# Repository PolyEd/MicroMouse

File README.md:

Hello! This is the central readme for the PolyEd MicroMouse Project. \
This file is a compilation of general (non-code specific) information relating to the project.

Our inspiration: \
[The Fastest Maze-Solving Competition On Earth](https://www.youtube.com/watch?v=ZMQbHMgK2rw)

The conference we will attend: \
[APEC](https://apec-conf.org/)

Rules:
- [The conference rules](https://s3.us-east-1.amazonaws.com/apec-conf-images/APEC_Policies_And_Procedures_Rev_7-3_2022-09-02.pdf) —\
  See page 15 "Minimum Age Policy" which implies there is no minimum age for the MicroMouse contest.
- [An old set of MicroMouse rules (revision 2009)](http://micromouseusa.com/wp-content/uploads/2013/10/APEC-Rules.pdf)

**Important** files to read before working with the Arduino code or using it:
- [I2C README](I2C-README.md)
- [Info about the plotting library used in this project](PLOTTER-README.md)

<!--
---
Also [Nim](https://nim-lang.org/) 😃
--><!--I (Joshua) commented this out to not be beligerent, please leave it in here in this form though, just for fun-->

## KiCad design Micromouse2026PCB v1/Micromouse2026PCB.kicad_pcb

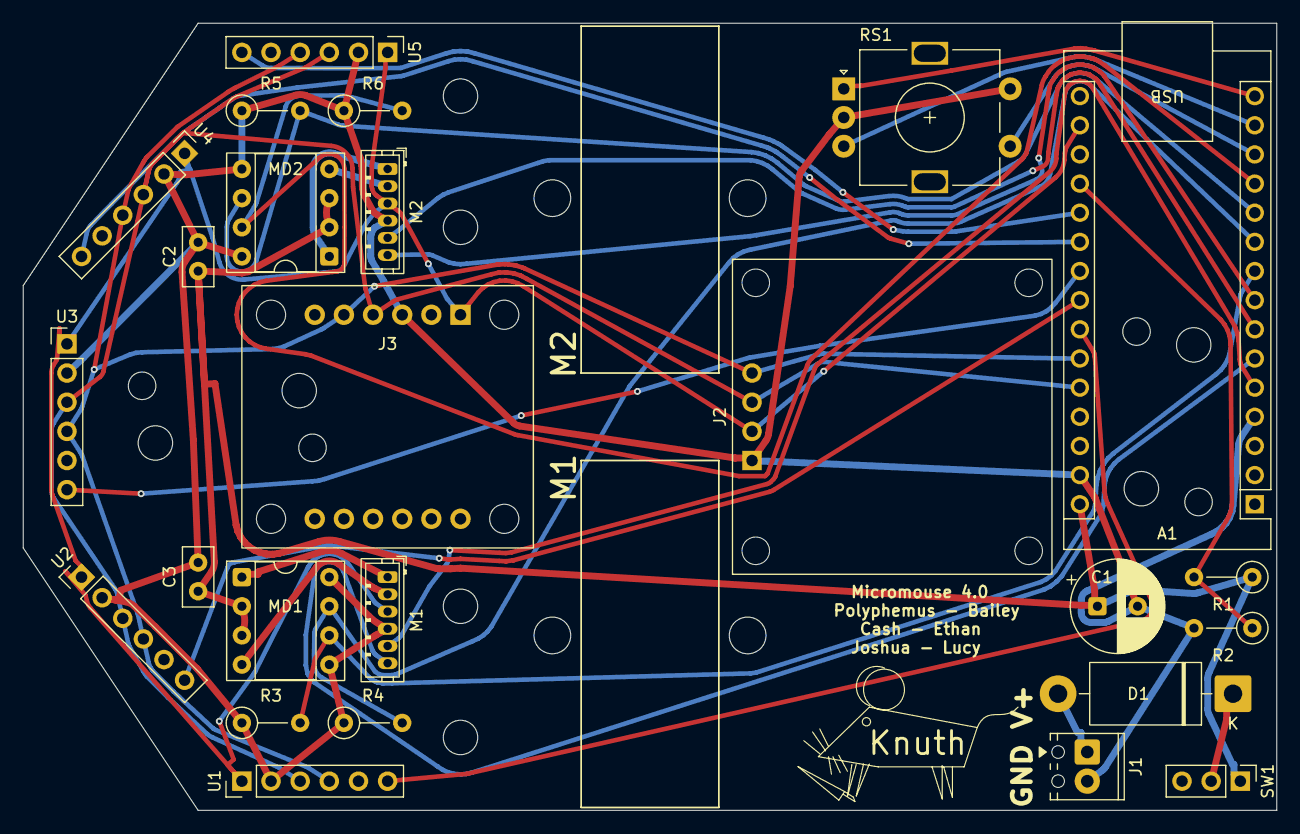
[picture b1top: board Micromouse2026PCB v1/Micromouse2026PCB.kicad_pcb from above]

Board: 2 copper layers, 109.2 x 68.6 mm, 25 parts (0 on the bottom side), 28 nets.

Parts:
A1: Arduino_Nano_ESP32; Arduino_Nano
C1: 470 µF (16v); CP_Radial_D8.0mm_P3.50mm
C2, C3: 100 nF; C_Disc_D5.0mm_W2.5mm_P2.50mm
D1: 1N5822; D_DO-201AD_P15.24mm_Horizontal
J1: Power Terminal; TerminalBlock_Phoenix_MPT-0,5-2-2.54_1x02_P2.54mm_Horizontal
J2: i2c OLED; OLED_0.96_SSD1306_I2C
J3: BNO085; Adafruit_BNO085
M1, M2: JST_ZH_B6B-ZR_1x06_P1.50mm_Vertical
MD1, MD2: DIP-8_W7.62mm_Socket
R1: 20k; R_Axial_DIN0207_L6.3mm_D2.5mm_P5.08mm_Vertical
R2, R3, R4, R5, R6: 10k; R_Axial_DIN0207_L6.3mm_D2.5mm_P5.08mm_Vertical
RS1: RotaryEncoder_Switch; RotaryEncoder_Alps_EC11E-Switch_Vertical_H20mm
SW1: PowerSW; PinHeader_1x03_P2.54mm_Vertical
U1, U2, U3, U4, U5: PinHeader_1x06_P2.54mm_Vertical

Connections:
+3.3V: A1.17 (3V3), J2.2, J3.1, M1.3 (VCC), M2.3 (VCC), U1.1 (VIN), U2.1 (VIN), U3.1 (VIN), U4.1 (VIN), U5.1 (VIN)
/SCL: A1.26 (A7), J2.3, J3.4, U1.3 (SCL), U2.3 (SCL), U3.3 (SCL), U4.3 (SCL), U5.3 (SCL)
/SDA: A1.25 (A6), J2.4, J3.5, U1.4 (SDA), U2.4 (SDA), U3.4 (SDA), U4.4 (SDA), U5.4 (SDA)
GND: A1.4 (GND), A1.29 (GND), C1.2, C2.2, C3.2, J1.2, J2.1, J3.3, M1.4 (GND), M2.4 (GND), MD1.5 (GND), MD1.8 (GND), MD2.5 (GND), MD2.8 (GND), R2.2, R3.1, R4.1, R5.1, R6.1, RS1.C, RS1.S2, U1.2 (GND), U2.2 (GND), U3.2 (GND), U4.2 (GND), U5.2 (GND)
unnamed: A1.19 (A0), R1.2, R2.1
unnamed: A1.20 (A1), U5.6 (XSHUT)
unnamed: A1.21 (A2), U4.6 (XSHUT)
unnamed: A1.22 (A3), U3.6 (XSHUT)
unnamed: A1.5 (D2), M1.5 (OA)
unnamed: A1.6 (D3), M1.6 (OB)
unnamed: A1.7 (D4), M2.5 (OA)
unnamed: A1.8 (D5), M2.6 (OB)
unnamed: A1.9 (D6), MD1.6 (IA), R3.2
unnamed: A1.10 (D7), MD1.7 (IB), R4.2
unnamed: A1.11 (D8), MD2.6 (IA), R5.2
unnamed: A1.12 (D9), MD2.7 (IB), R6.2
unnamed: A1.13 (D10/CS), RS1.S1
unnamed: A1.14 (D11/COPI), RS1.B
unnamed: A1.15 (D12/CIPO), RS1.A
unnamed: A1.24 (SCL/A5), U1.6 (XSHUT)
unnamed: A1.23 (SDA/A4), U2.6 (XSHUT)
unnamed: A1.30 (VIN), C1.1, C2.1, C3.1, MD1.2 (VCC), MD1.3 (VCC), MD2.2 (VCC), MD2.3 (VCC), R1.1, SW1.1
unnamed: D1.2 (A), J1.1
unnamed: D1.1 (K), SW1.2
unnamed: M1.1 (MA), MD1.1 (OA)
unnamed: M1.2 (MB), MD1.4 (OB)
unnamed: M2.1 (MA), MD2.1 (OA)
unnamed: M2.2 (MB), MD2.4 (OB)

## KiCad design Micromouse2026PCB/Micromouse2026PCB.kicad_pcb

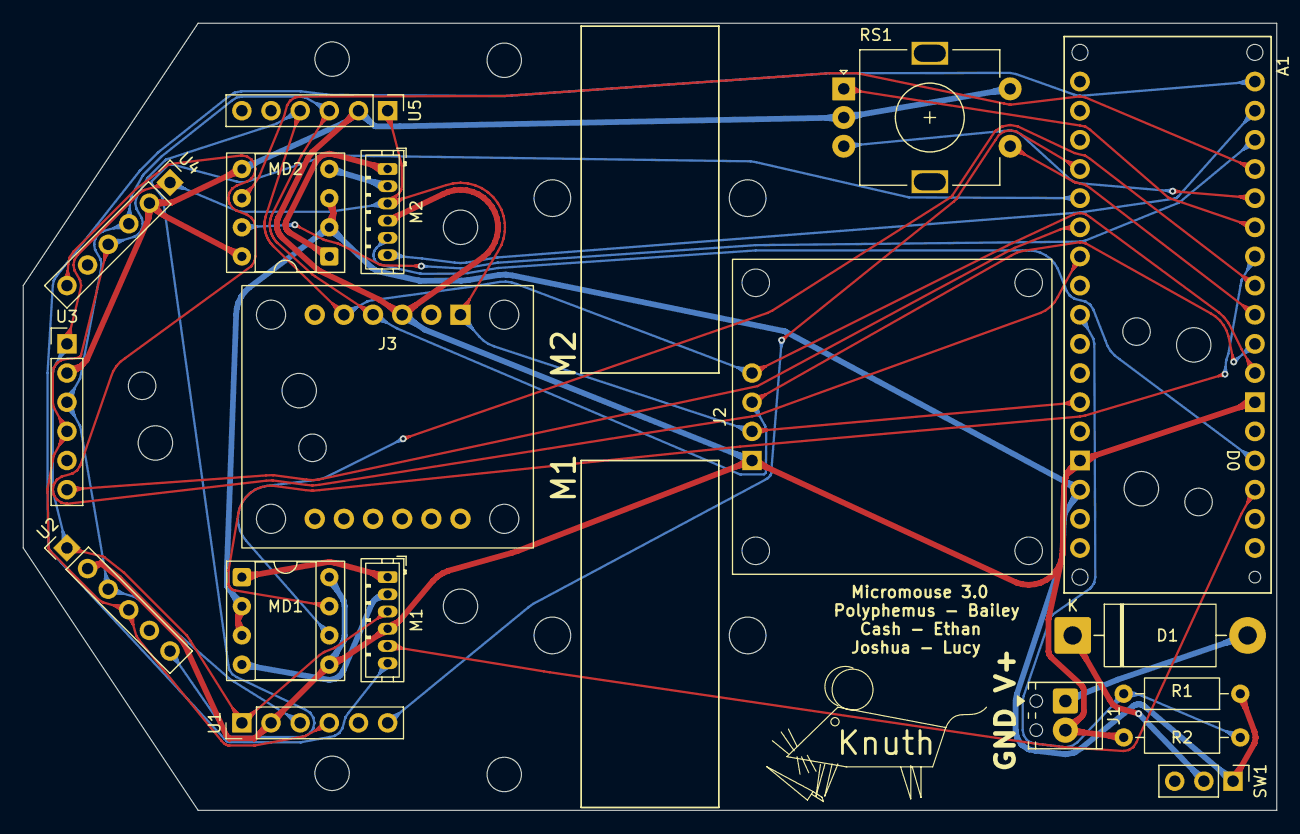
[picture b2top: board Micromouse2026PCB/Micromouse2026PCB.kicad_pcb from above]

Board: 2 copper layers, 109.2 x 68.6 mm, 18 parts (0 on the bottom side), 27 nets.

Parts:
A1: Arduino_Micro_Socket
D1: 1N5822; D_DO-201AD_P15.24mm_Horizontal
J1: Power Terminal; TerminalBlock_Phoenix_MPT-0,5-2-2.54_1x02_P2.54mm_Horizontal
J2: i2c OLED; OLED_0.96_SSD1306_I2C
J3: BNO085; Adafruit_BNO085
M1, M2: JST_ZH_B6B-ZR_1x06_P1.50mm_Vertical
MD1, MD2: DIP-8_W7.62mm_Socket
R1, R2: 10k; R_Axial_DIN0207_L6.3mm_D2.5mm_P10.16mm_Horizontal
RS1: RotaryEncoder_Switch; RotaryEncoder_Alps_EC11E-Switch_Vertical_H20mm
SW1: PowerSW; PinHeader_1x03_P2.54mm_Vertical
U1, U2, U3, U4, U5: PinHeader_1x06_P2.54mm_Vertical

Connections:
+5V: A1.5V, J2.2, J3.1, M1.3 (VCC), M2.3 (VCC), U1.1 (VIN), U2.1 (VIN), U3.1 (VIN), U4.1 (VIN), U5.1 (VIN)
/SCL: A1.D3 (D3/SCL), J2.3, J3.4, U1.3 (SCL), U2.3 (SCL), U3.3 (SCL), U4.3 (SCL), U5.3 (SCL)
/SDA: A1.D2 (D2/SDA), J2.4, J3.5, U1.4 (SDA), U2.4 (SDA), U3.4 (SDA), U4.4 (SDA), U5.4 (SDA)
GND: A1.GND1 (GND), A1.GND2 (GND), J1.2, J2.1, J3.3, M1.4 (GND), M2.4 (GND), MD1.5 (GND), MD1.8 (GND), MD2.5 (GND), MD2.8 (GND), R2.2, RS1.C, RS1.S2, U1.2 (GND), U2.2 (GND), U3.2 (GND), U4.2 (GND), U5.2 (GND)
unnamed: A1.D0 (D0/RX), M2.5 (OA)
unnamed: A1.D1 (D1/TX), M1.5 (OA)
unnamed: A1.D7 (D7_INT4), RS1.A
unnamed: A1.A5, R1.2, R2.1
unnamed: A1.D4, RS1.S1
unnamed: A1.D8, RS1.B
unnamed: D1.2 (A), J1.1
unnamed: D1.1 (K), SW1.2
unnamed: M1.1 (MA), MD1.1 (OA)
unnamed: M1.2 (MB), MD1.4 (OB)
unnamed: A1.D12, M1.6 (OB)
unnamed: M2.1 (MA), MD2.1 (OA)
unnamed: M2.2 (MB), MD2.4 (OB)
unnamed: A1.D11, M2.6 (OB)
unnamed: A1.D5, MD1.6 (IA)
unnamed: A1.D6, MD1.7 (IB)
unnamed: A1.D9, MD2.6 (IA)
unnamed: A1.D10, MD2.7 (IB)
unnamed: A1.VIN, MD1.2 (VCC), MD1.3 (VCC), MD2.2 (VCC), MD2.3 (VCC), R1.1, SW1.1
unnamed: A1.A0, U1.6 (XSHUT)
unnamed: A1.A1, U2.6 (XSHUT)
unnamed: A1.A2, U3.6 (XSHUT)
unnamed: A1.A3, U4.6 (XSHUT)

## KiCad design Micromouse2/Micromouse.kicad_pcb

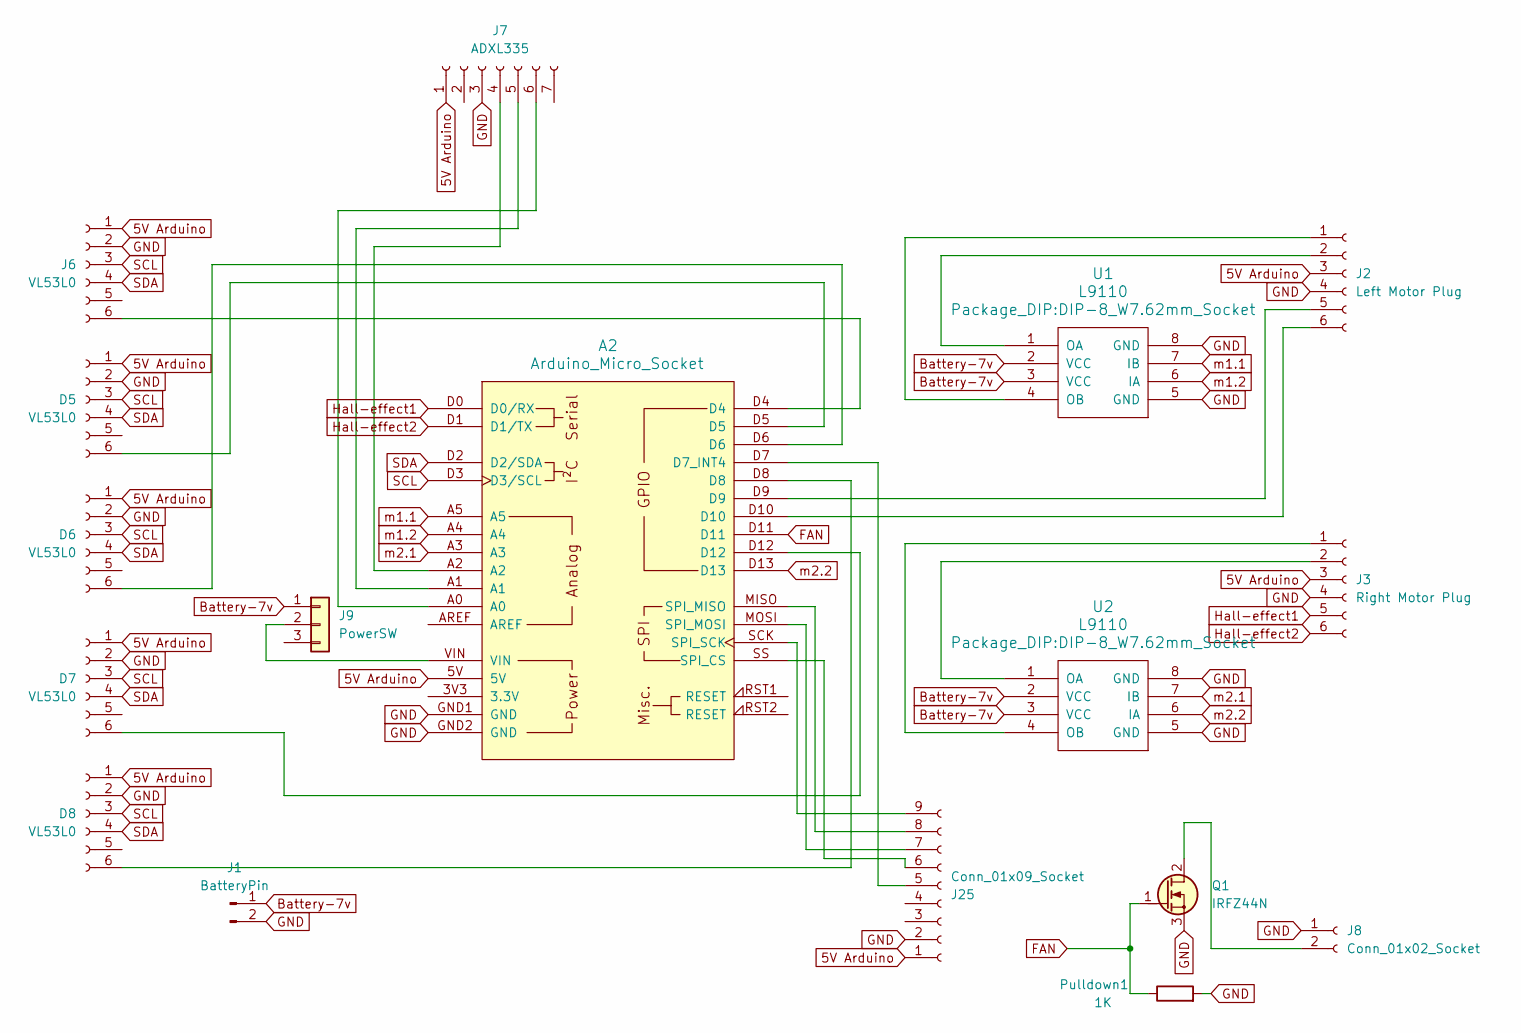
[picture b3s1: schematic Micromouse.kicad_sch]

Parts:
A2: Arduino_Micro_Socket
D5, D6, D7, D8: VL53L0; PinSocket_1x06_P2.54mm_Vertical
J1: BatteryPin; PinSocket_1x02_P2.54mm_Vertical
J2: Left Motor Plug; Wuerth_WR-WTB_64800611622_1x06_P1.50mm_Vertical
J3: Right Motor Plug; Wuerth_WR-WTB_64800611622_1x06_P1.50mm_Vertical
J6: VL53L0; PinSocket_1x06_P2.54mm_Vertical
J7: ADXL335; PinSocket_1x07_P2.54mm_Vertical
J8: Conn_01x02_Socket; JST_PH_B2B-PH-K_1x02_P2.00mm_Vertical
J9: PowerSW; PinHeader_1x03_P2.54mm_Vertical
J25: Conn_01x09_Socket; PinHeader_1x09_P2.54mm_Horizontal
Pulldown1: 1K; R_Axial_DIN0207_L6.3mm_D2.5mm_P7.62mm_Horizontal
Q1: IRFZ44N; TO-220-3_Horizontal_TabDown
U1, U2: L9110; DIP-8_W7.62mm_Socket

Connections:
5V Arduino: A2.5V, D5.1 (Vin), D6.1 (Vin), D7.1 (Vin), D8.1 (Vin), J2.3, J3.3, J6.1 (Vin), J7.1, J25.1
Battery-7v: J1.1, J9.1, U1.2 (VCC), U1.3 (VCC), U2.2 (VCC), U2.3 (VCC)
FAN: A2.D11, Pulldown1.1, Q1.1 (G)
GND: A2.GND1 (GND), A2.GND2 (GND), D5.2 (GND), D6.2 (GND), D7.2 (GND), D8.2 (GND), J1.2, J2.4, J3.4, J6.2 (GND), J7.3, J8.1, J25.2, Pulldown1.2, Q1.3 (S), U1.5 (GND), U1.8 (GND), U2.5 (GND), U2.8 (GND)
Hall-effect1: A2.D0 (D0/RX), J3.5
Hall-effect2: A2.D1 (D1/TX), J3.6
unnamed: A2.D7 (D7_INT4), J25.5
unnamed: A2.SS (SPI_CS), J25.6
unnamed: A2.MISO (SPI_MISO), J25.8
unnamed: A2.MOSI (SPI_MOSI), J25.7
unnamed: A2.SCK (SPI_SCK), J25.9
unnamed: A2.D5, D5.6 (XSHUT)
unnamed: A2.D6, D6.6 (XSHUT)
unnamed: A2.D12, D7.6 (XSHUT)
unnamed: A2.D8, D8.6 (XSHUT)
unnamed: J2.1, U1.4 (OB)
unnamed: J2.2, U1.1 (OA)
unnamed: A2.D9, J2.5
unnamed: A2.D10, J2.6
unnamed: J3.1, U2.4 (OB)
unnamed: J3.2, U2.1 (OA)
unnamed: A2.D4, J6.6 (XSHUT)
unnamed: A2.A2, J7.4
unnamed: A2.A1, J7.5
unnamed: A2.A0, J7.6
unnamed: J8.2, Q1.2 (D)
unnamed: A2.VIN, J9.2
SCL: A2.D3 (D3/SCL), D5.3 (SCL), D6.3 (SCL), D7.3 (SCL), D8.3 (SCL), J6.3 (SCL)
SDA: A2.D2 (D2/SDA), D5.4 (SDA), D6.4 (SDA), D7.4 (SDA), D8.4 (SDA), J6.4 (SDA)
m1.1: A2.A5, U1.7 (IB)
m1.2: A2.A4, U1.6 (IA)
m2.1: A2.A3, U2.7 (IB)
m2.2: A2.D13, U2.6 (IA)

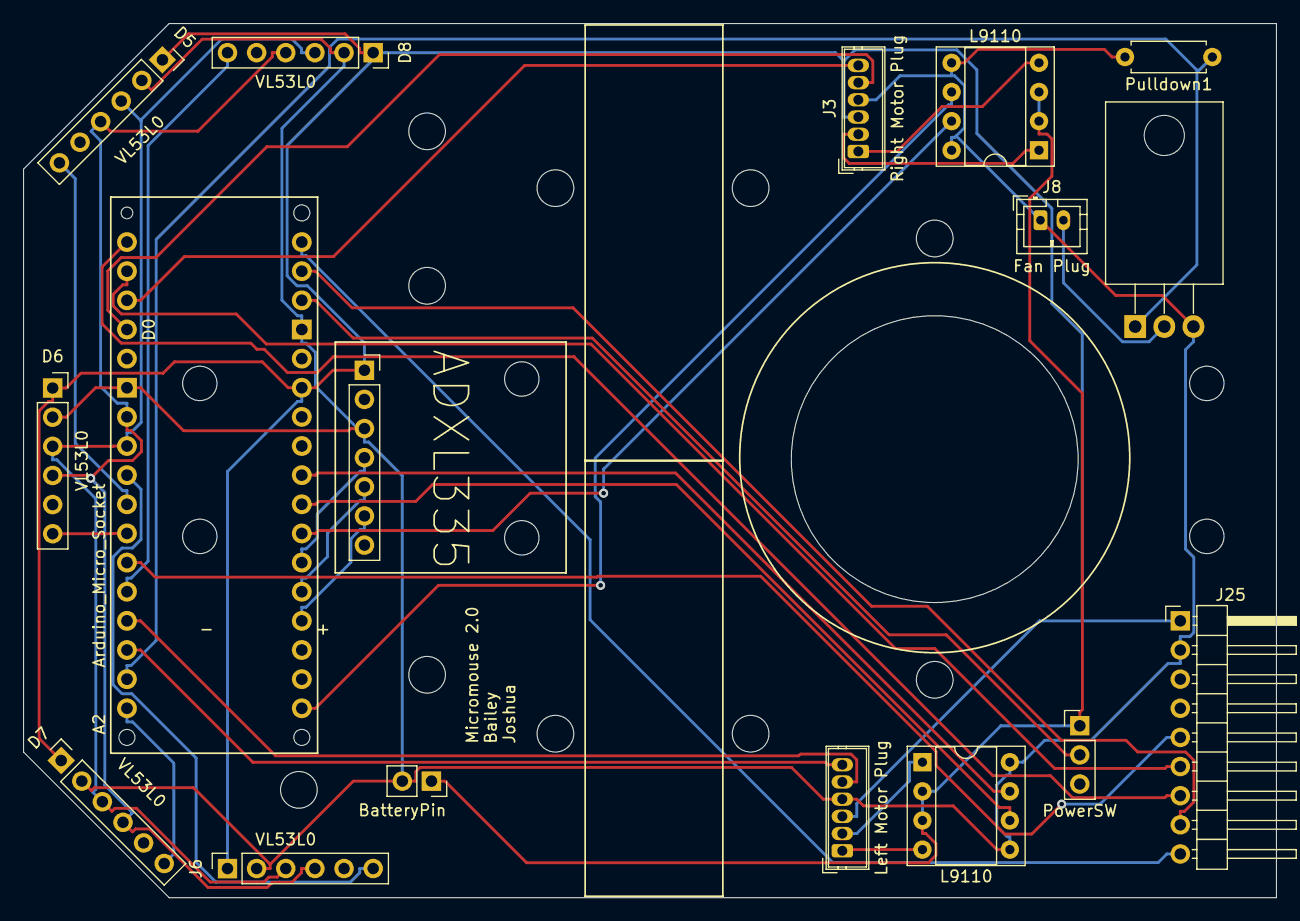
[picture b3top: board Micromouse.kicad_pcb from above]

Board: 2 copper layers, 109.2 x 76.2 mm, 17 parts (0 on the bottom side), 33 nets.

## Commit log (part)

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2023-09-01 Update main.c
    now it has a main function
2023-09-01 Create README.txt
    added initial setup
2023-09-01 Create makefile
2023-09-01 Update makefile
2023-09-01 Fix up makefile
2023-09-04 Update README.txt
    added a space
2023-09-14 Create Arduino Uno Rev3 folder
2023-09-14 Add eagle files + schematics + other info
2023-09-14 Update README.txt
    added old ruleset
2023-09-14 A bunch of files for micromouse related projects
2023-09-16 Create old micromouse
2023-09-21 Added info about HMC5883
2023-09-22 Cleaned up README.md
    - Changed to use proper Markdown formatting for links
    - Removed the unnecessary and excessively-used `<br>`s and replaced them with `\`s at the end of lines to follow standard practice and to improve readability of Markdown source
    - Changed the writing to be more concise.
2023-09-25 Clarify some instructions and fix MD syntax
2023-09-29 Added ADXL335 info
2023-09-29 Move README for ADXL335 to correct directory
2023-10-11 Added info on I2C, plotting, and the VL53L0X.
2023-10-12 Update README.md to fix typo
2023-10-12 Add plotter code for ADXL335
2023-10-26 Added Pro Micro Eagle File
2023-10-26 Add N20 Gear Motor Connector Eagle File
2023-10-26 Changed Structure
2023-10-28 Added datasheets
2023-10-28 Create floodFillInC
2024-01-20 Update Eagle Design
2024-02-09 added labels
2024-10-24 thingamajig
2024-10-25 add try catch
2024-11-08 gtgt6gt6
    tvtgtygvgyguyygugy
2025-01-17 Reorganize file structure
2025-04-24 Add Disambiguation for some code and fix bug in microsuite noble
2025-05-29 add straight code (current version)
